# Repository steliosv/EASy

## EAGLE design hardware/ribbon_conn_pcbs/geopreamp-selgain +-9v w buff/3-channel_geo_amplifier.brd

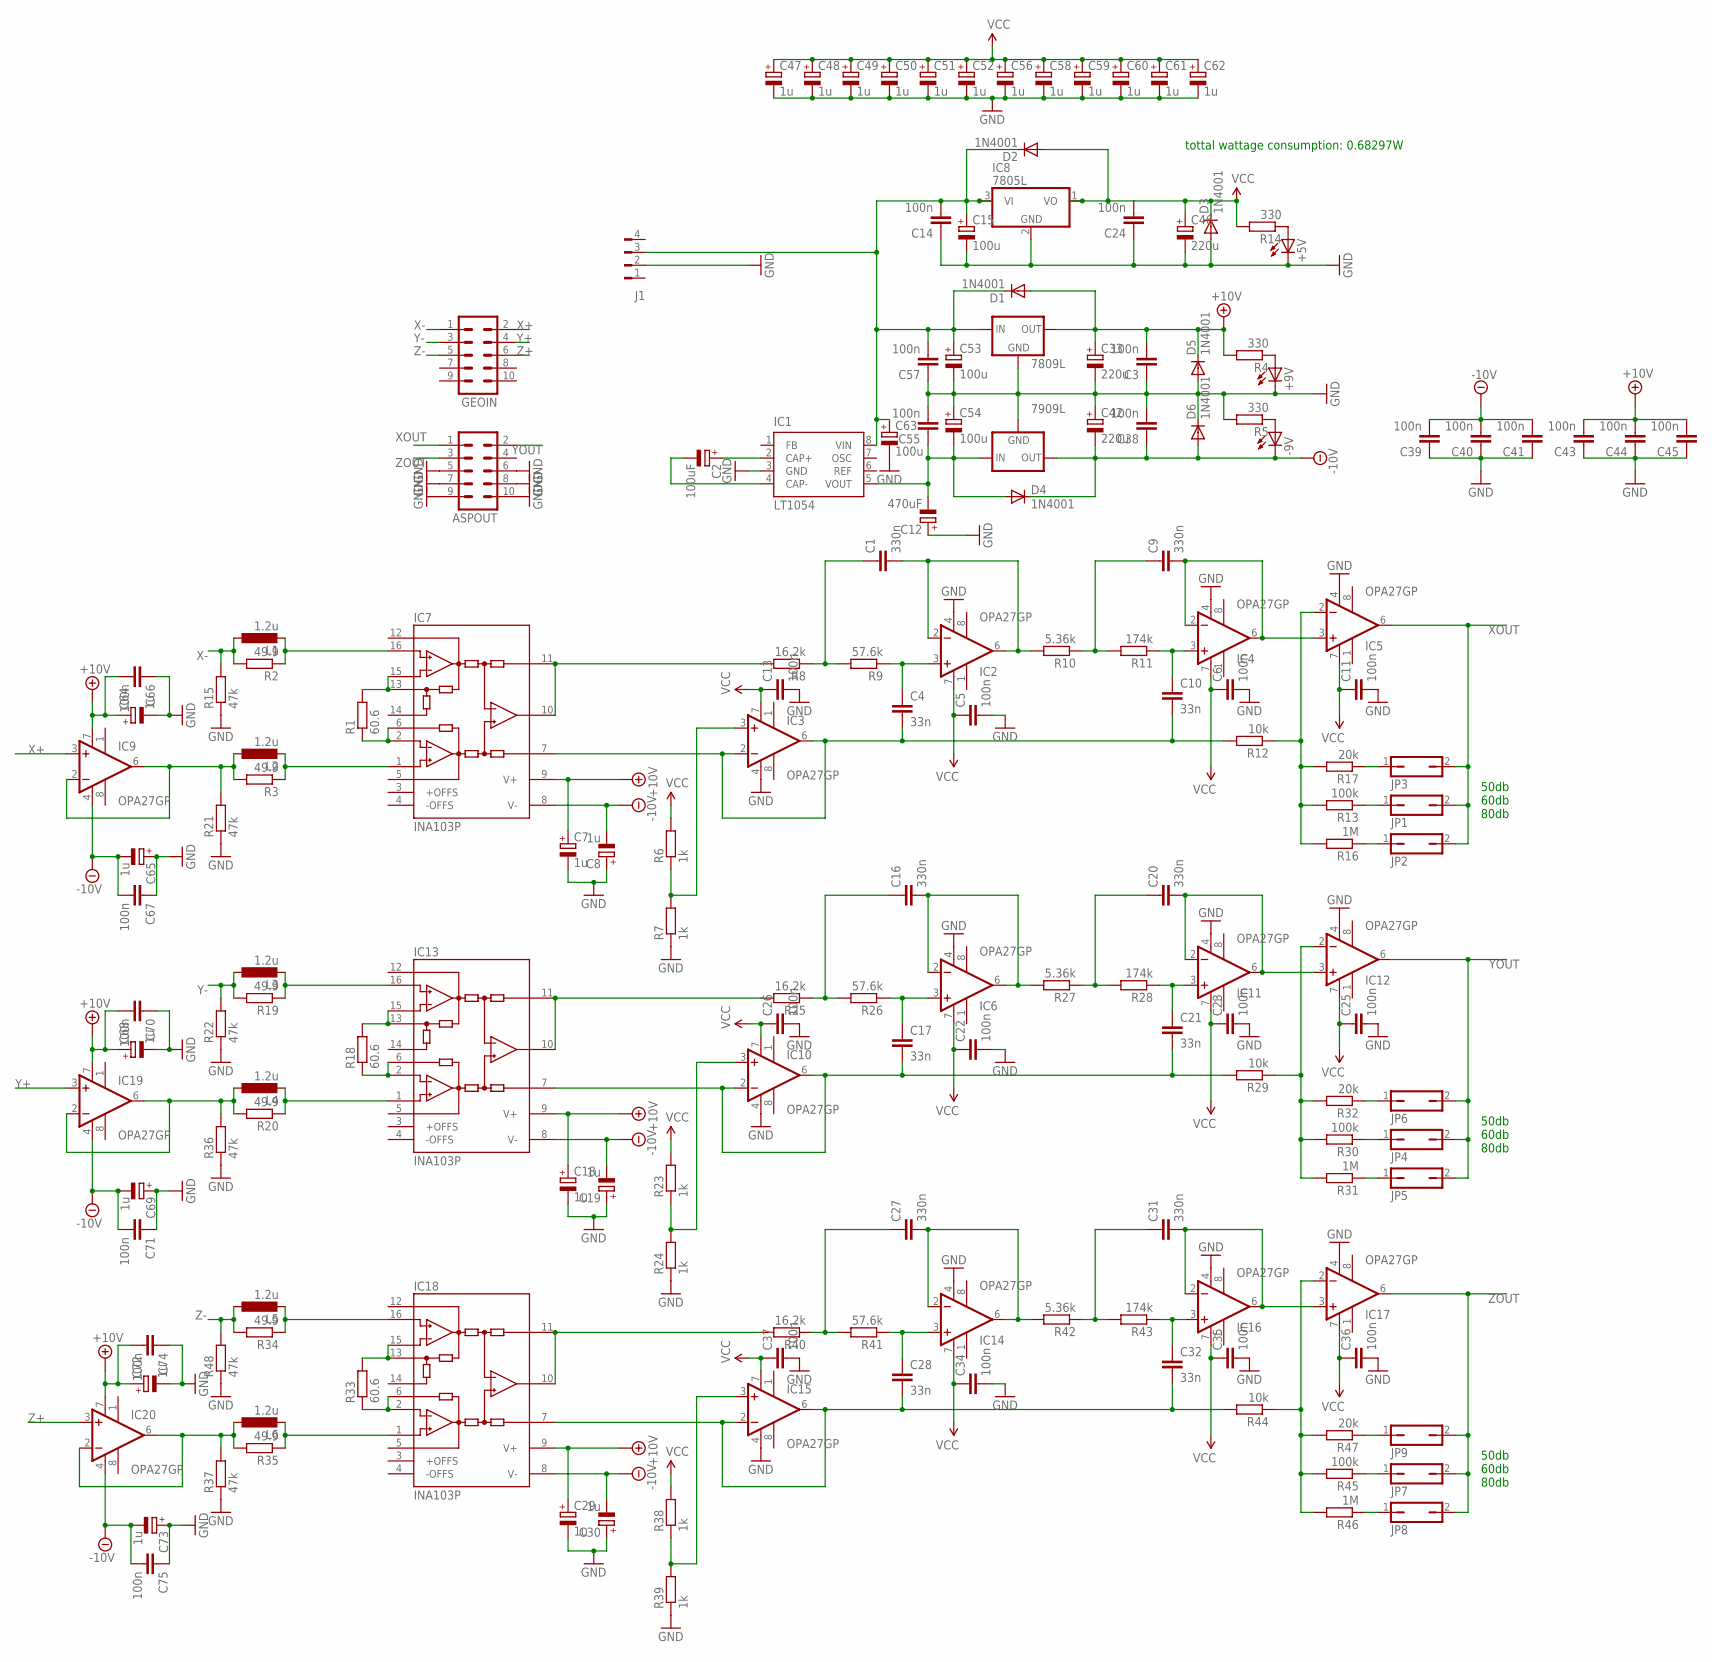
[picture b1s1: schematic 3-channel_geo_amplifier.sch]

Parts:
7809L: 78LXX
7909L: 79LXX
+5V, +9V: LED3MM
-9V: LED3MM
ASPOUT: ML10
C1, C9, C16, C20, C27, C31: 330n; C050-025X075
C2: 100uF; E2,5-7
C3, C5, C6, C11, C13, C14, C22, C23, C24, C25, C26, C34, C35, C36, C37, C38, C39, C40, C41, C43, C44, C45, C55, C57, C66, C67, C70, C71, C74, C75: 100n; C050-025X075
C4, C10, C17, C21, C28, C32: 33n; C050-025X075
C7, C8, C18, C19, C29, C30, C47, C48, C49, C50, C51, C52, C56, C58, C59, C60, C61, C62, C64, C65, C68, C69, C72, C73: 1u; B45181A
C12: 470uF; E5-8,5
C15: 100u; E2,5-7
C33, C42: 220u; E2,5-5
C46: 220u; E2,5-7
C53, C54, C63: 100u; E2,5-5
D1, D2, D3, D4, D5, D6: 1N4001; DO41-10
GEOIN: ML10
IC1: LT1054; DIL8
IC2, IC3, IC4, IC5, IC6, IC9, IC10, IC11, IC12, IC14, IC15, IC16, IC17, IC19, IC20: OPA27GP; DIL08
IC7, IC13, IC18: INA103P; DIL16
IC8: 7805L; TO92
J1: FLOP-4W827001; 827001
JP1, JP2, JP3, JP4, JP5, JP6, JP7, JP8, JP9: JP1Q; JP1
L1, L2, L3, L4, L5, L6: 1.2u; 0207/10
R1, R18, R33: 60.6; 0207/10
R2, R3, R19, R20, R34, R35: 49.9; 0207/10
R4, R5, R14: 330; 0207/10
R6, R7, R23, R24, R38, R39: 1k; 0207/10
R8, R25, R40: 16.2k; 0207/10
R9, R26, R41: 57.6k; 0207/10
R10, R27, R42: 5.36k; 0207/10
R11, R28, R43: 174k; 0207/10
R12, R29, R44: 10k; 0207/10
R13, R30, R45: 100k; 0207/10
R15, R21, R22, R36, R37, R48: 47k; 0207/10
R16, R31, R46: 1M; 0207/10
R17, R32, R47: 20k; 0207/10

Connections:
+10V: 7809L.OUT, C3.2, C7.+, C18.+, C29.+, C33.+, C43.2, C44.2, C45.2, C64.+, C66.2, C68.+, C70.2, C72.+, C74.2, D1.A, D5.C, IC7.9 (V+), IC9.7 (V+), IC13.9 (V+), IC18.9 (V+), IC19.7 (V+), IC20.7 (V+), R4.2
-10V: 7909L.OUT, -9V.K (C), C8.-, C19.-, C30.-, C38.1, C39.2, C40.2, C41.2, C42.-, C65.-, C67.2, C69.-, C71.2, C73.-, C75.2, D4.C, D6.A, IC7.8 (V-), IC9.4 (V-), IC13.8 (V-), IC18.8 (V-), IC19.4 (V-), IC20.4 (V-)
A: IC20.2 (-IN), IC20.6 (OUT), L6.1, R35.2, R37.2
GND: 7809L.GND, 7909L.GND, +5V.K (C), +9V.K (C), ASPOUT.5, ASPOUT.6, ASPOUT.7, ASPOUT.8, ASPOUT.9, ASPOUT.10, C3.1, C5.2, C6.2, C7.-, C8.+, C11.2, C12.+, C13.2, C14.1, C15.-, C18.-, C19.+, C22.2, C23.2, C24.1, C25.2, C26.2, C29.-, C30.+, C33.-, C34.2, C35.2, C36.2, C37.2, C38.2, C39.1, C40.1, C41.1, C42.+, C43.1, C44.1, C45.1, C46.-, C47.-, C48.-, C49.-, C50.-, C51.-, C52.-, C53.-, C54.+, C55.2, C56.-, C57.1, C58.-, C59.-, C60.-, C61.-, C62.-, C63.-, C64.-, C65.+, C66.1, C67.1, C68.-, C69.+, C70.1, C71.1, C72.-, C73.+, C74.1, C75.1, D3.A, D5.A, D6.C, IC1.3 (GND), IC2.4 (V-), IC3.4 (V-), IC4.4 (V-), IC5.4 (V-), IC6.4 (V-), IC8.2 (GND), IC10.4 (V-), IC11.4 (V-), IC12.4 (V-), IC14.4 (V-), IC15.4 (V-), IC16.4 (V-), IC17.4 (V-), J1.2, R5.2, R7.1, R15.1, R21.1, R22.1, R24.1, R36.1, R37.1, R39.1, R48.1
unnamed: IC7.13 (-RG), IC7.15 (-GS), R1.2
unnamed: IC7.2 (+GS), IC7.6 (+RG), R1.1
unnamed: IC7.1 (+IN), L2.2, R3.1
unnamed: IC19.2 (-IN), IC19.6 (OUT), L4.1, R20.2, R36.2
unnamed: IC7.16 (-IN), L1.2, R2.1
unnamed: C4.2, C10.2, IC3.2 (-IN), IC3.6 (OUT), IC7.7 (REF), R12.2
unnamed: IC3.3 (+IN), R6.1, R7.2
unnamed: IC7.10 (OUT), IC7.11 (SENSE), R8.2
unnamed: C1.1, R8.1, R9.2
unnamed: C4.1, IC2.3 (+IN), R9.1
unnamed: C1.2, IC2.2 (-IN), IC2.6 (OUT), R10.2
unnamed: C9.2, IC4.2 (-IN), IC4.6 (OUT), IC5.3 (+IN)
unnamed: C9.1, R10.1, R11.2
unnamed: C10.1, IC4.3 (+IN), R11.1
unnamed: +5V.A, R14.1
unnamed: IC5.2 (-IN), R12.1, R13.2, R16.2, R17.2
unnamed: JP1.1, R13.1
unnamed: IC9.2 (-IN), IC9.6 (OUT), L2.1, R3.2, R21.2
unnamed: +9V.A, R4.1
unnamed: IC13.13 (-RG), IC13.15 (-GS), R18.2
unnamed: JP2.1, R16.1
unnamed: IC13.2 (+GS), IC13.6 (+RG), R18.1
unnamed: JP3.1, R17.1
unnamed: IC13.1 (+IN), L4.2, R20.1
unnamed: C2.-, IC1.4 (CAP-)
unnamed: C2.+, IC1.2 (CAP+)
unnamed: IC13.16 (-IN), L3.2, R19.1
unnamed: C17.2, C21.2, IC10.2 (-IN), IC10.6 (OUT), IC13.7 (REF), R29.2
unnamed: IC10.3 (+IN), R23.1, R24.2
unnamed: IC13.10 (OUT), IC13.11 (SENSE), R25.2
unnamed: C16.1, R25.1, R26.2
unnamed: C17.1, IC6.3 (+IN), R26.1
unnamed: C16.2, IC6.2 (-IN), IC6.6 (OUT), R27.2
unnamed: C20.1, R27.1, R28.2
unnamed: C21.1, IC11.3 (+IN), R28.1
unnamed: C20.2, IC11.2 (-IN), IC11.6 (OUT), IC12.3 (+IN)
unnamed: IC12.2 (-IN), R29.1, R30.2, R31.2, R32.2
unnamed: -9V.A, R5.1
unnamed: JP4.1, R30.1
unnamed: JP5.1, R31.1
unnamed: JP6.1, R32.1
unnamed: IC18.13 (-RG), IC18.15 (-GS), R33.2
unnamed: IC18.2 (+GS), IC18.6 (+RG), R33.1
unnamed: IC18.1 (+IN), L6.2, R35.1
unnamed: 7809L.IN, C14.2, C15.+, C53.+, C57.2, C63.+, D1.C, D2.C, IC1.8 (VIN), IC8.3 (VI), J1.3
unnamed: IC18.16 (-IN), L5.2, R34.1
unnamed: C28.2, C32.2, IC15.2 (-IN), IC15.6 (OUT), IC18.7 (REF), R44.2
unnamed: IC15.3 (+IN), R38.1, R39.2
unnamed: IC18.10 (OUT), IC18.11 (SENSE), R40.2
unnamed: C27.1, R40.1, R41.2
unnamed: C28.1, IC14.3 (+IN), R41.1
unnamed: 7909L.IN, C12.-, C54.-, C55.1, D4.A, IC1.5 (VOUT)
unnamed: C27.2, IC14.2 (-IN), IC14.6 (OUT), R42.2
unnamed: C31.1, R42.1, R43.2
unnamed: C32.1, IC16.3 (+IN), R43.1
unnamed: C31.2, IC16.2 (-IN), IC16.6 (OUT), IC17.3 (+IN)
unnamed: IC17.2 (-IN), R44.1, R45.2, R46.2, R47.2
unnamed: JP7.1, R45.1
unnamed: JP8.1, R46.1
unnamed: JP9.1, R47.1
VCC: C5.1, C6.1, C11.1, C13.1, C22.1, C23.1, C24.2, C25.1, C26.1, C34.1, C35.1, C36.1, C37.1, C46.+, C47.+, C48.+, C49.+, C50.+, C51.+, C52.+, C56.+, C58.+, C59.+, C60.+, C61.+, C62.+, D2.A, D3.C, IC2.7 (V+), IC3.7 (V+), IC4.7 (V+), IC5.7 (V+), IC6.7 (V+), IC8.1 (VO), IC10.7 (V+), IC11.7 (V+), IC12.7 (V+), IC14.7 (V+), IC15.7 (V+), IC16.7 (V+), IC17.7 (V+), R6.2, R14.2, R23.2, R38.2
X+: GEOIN.2, IC9.3 (+IN)
X-: GEOIN.1, L1.1, R2.2, R15.2
XOUT: ASPOUT.1, IC5.6 (OUT), JP1.2, JP2.2, JP3.2
Y+: GEOIN.4, IC19.3 (+IN)
Y-: GEOIN.3, L3.1, R19.2, R22.2
YOUT: ASPOUT.2, IC12.6 (OUT), JP4.2, JP5.2, JP6.2
Z+: GEOIN.6, IC20.3 (+IN)
Z-: GEOIN.5, L5.1, R34.2, R48.2
ZOUT: ASPOUT.3, IC17.6 (OUT), JP7.2, JP8.2, JP9.2

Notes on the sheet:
50db 60db 80db
tottal wattage consumption: 0.68297W

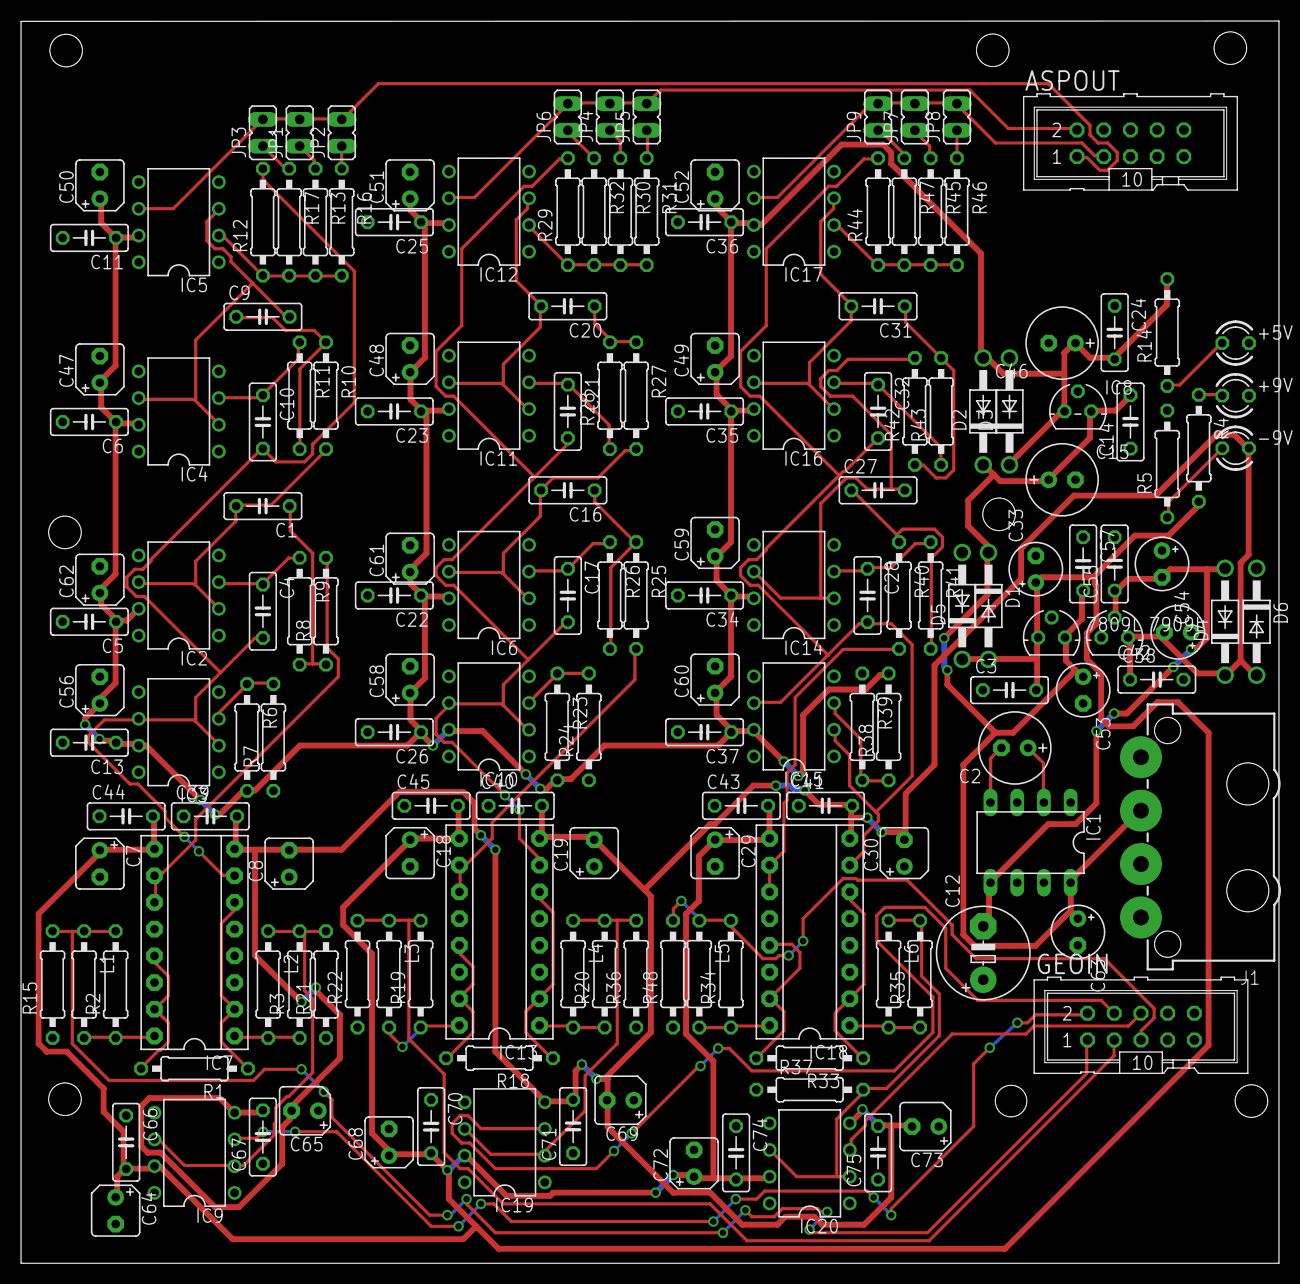
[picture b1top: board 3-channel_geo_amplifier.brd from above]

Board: 2 copper layers, 119.6 x 118.1 mm, 172 parts (0 on the bottom side), 74 nets.

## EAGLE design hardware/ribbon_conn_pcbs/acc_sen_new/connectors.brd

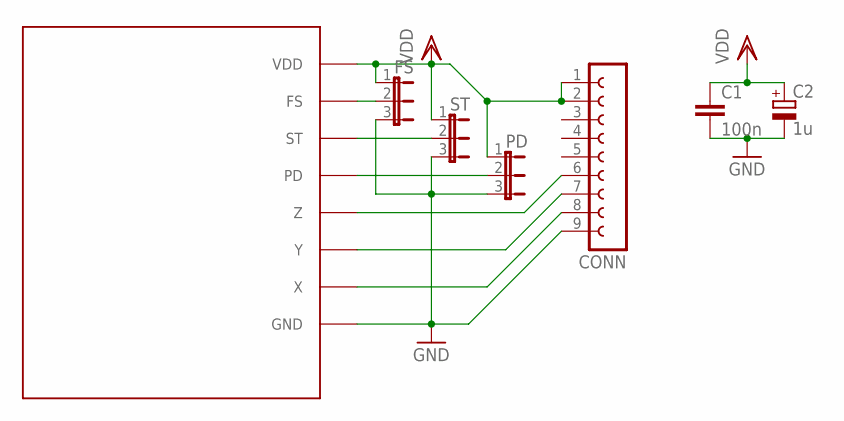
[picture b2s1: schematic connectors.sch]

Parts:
C1: 100n; C050-025X075
C2: 1u; E2-5
CONN: FE09-1; FE09
FS: JP2E; JP2
PD: JP2E; JP2
ST: JP2E; JP2
U$2: LIS; LIS344

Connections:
GND: C1.2, C2.-, CONN.9, FS.3, PD.3, ST.3, U$2.GND1 (GND), U$2.GND2 (GND), U$2.GND3 (GND), U$2.GND5 (GND)
unnamed: CONN.8, U$2.X
unnamed: FS.2, U$2.FS
unnamed: CONN.7, U$2.Y
unnamed: CONN.6, U$2.Z
unnamed: ST.2, U$2.ST
unnamed: PD.2, U$2.PD
VDD: C1.1, C2.+, CONN.1, CONN.2, FS.1, PD.1, ST.1, U$2.VDD, U$2.VDD2 (VDD)

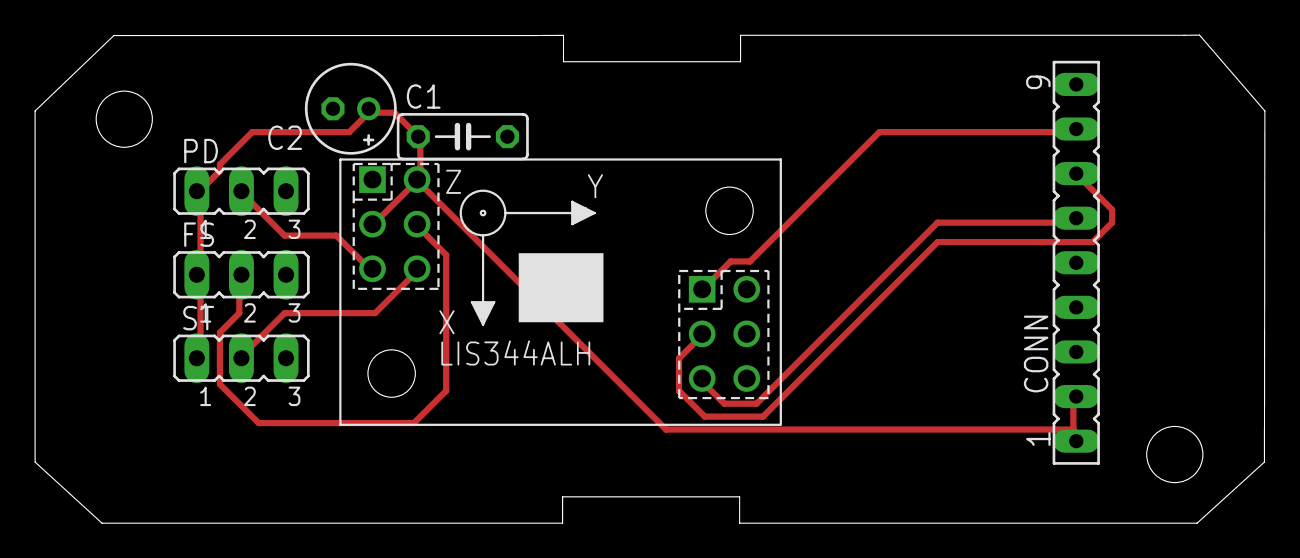
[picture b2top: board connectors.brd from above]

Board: 2 copper layers, 70.1 x 27.8 mm, 7 parts (0 on the bottom side), 8 nets.

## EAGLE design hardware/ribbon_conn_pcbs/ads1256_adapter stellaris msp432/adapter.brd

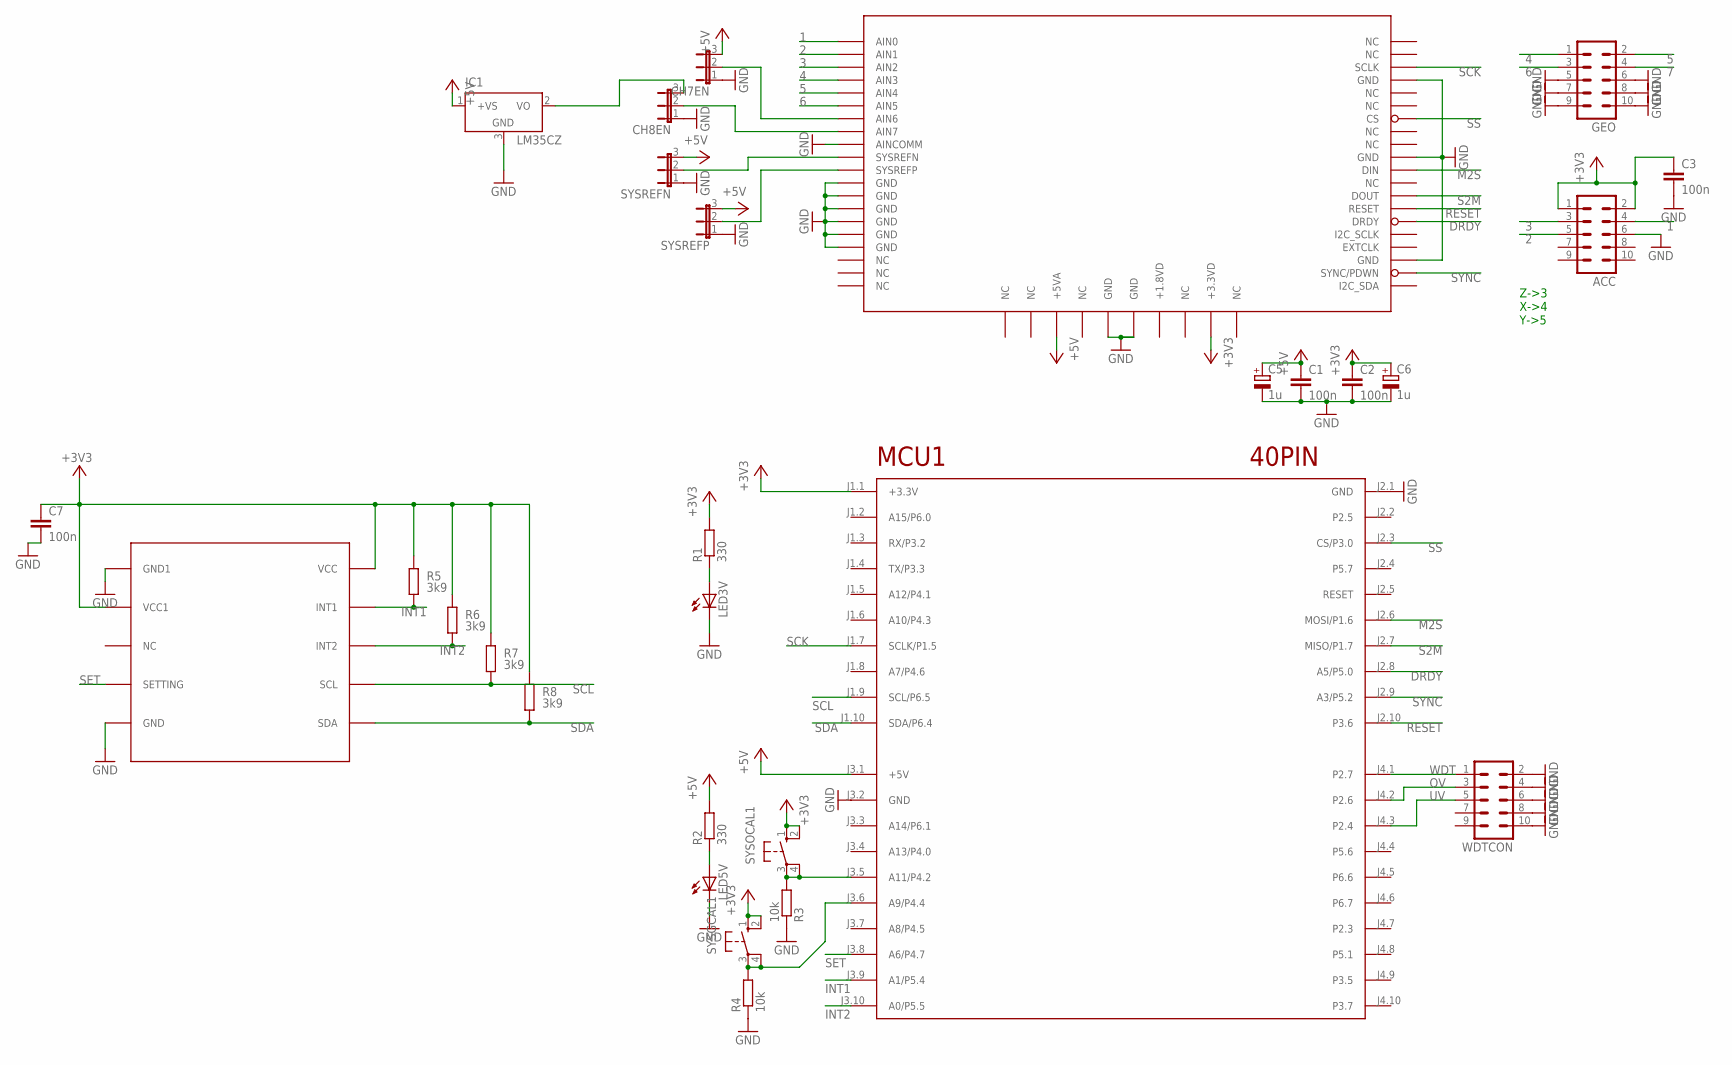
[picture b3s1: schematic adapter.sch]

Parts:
ACC: ML10
C1, C2, C3, C7: 100n; C050-025X075
C5, C6: 1u; E2,5-6E
CH7EN, CH8EN: JP2E; JP2
GEO: ML10
IC1: LM35CZ; TO92
LED3V, LED5V: LED3MM
MCU1: 40PIN
R1, R2: 330; 0207/10
R3, R4: 10k; 0207/10
R5, R6, R7, R8: 3k9; 0207/10; TOLERANCE 5%
SYSGCAL1: 10-XX; B3F-10XX
SYSOCAL1: 10-XX; B3F-10XX
SYSREFN: JP2E; JP2
SYSREFP: JP2E; JP2
U$1: D7S
U$2: ADS1256EVM
WDTCON: ML10

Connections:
1: ACC.4, U$2.J1.1 (AIN0)
2: ACC.5, U$2.J1.2 (AIN1)
3: ACC.3, U$2.J1.3 (AIN2)
4: GEO.1, U$2.J1.4 (AIN3)
5: GEO.2, U$2.J1.5 (AIN4)
6: GEO.3, U$2.J1.6 (AIN5)
7: GEO.4
+3V3: ACC.1, ACC.2, C2.1, C3.1, C6.+, C7.1, MCU1.J1.1 (+3.3V), R1.2, R5.2, R6.2, R7.2, R8.2, SYSGCAL1.1 (S), SYSGCAL1.2 (S1), SYSOCAL1.1 (S), SYSOCAL1.2 (S1), U$1.P$1 (VCC), U$1.P$9 (VCC1), U$2.J3.9 (+3.3VD)
+5V: C1.1, C5.+, CH7EN.3, IC1.1 (+VS), MCU1.J3.1 (+5V), R2.2, SYSREFN.3, SYSREFP.3, U$2.J3.3 (+5VA)
DRDY: MCU1.J2.8 (A5/P5.0), U$2.J2.15 (DRDY)
GND: ACC.6, C1.2, C2.2, C3.2, C5.-, C6.-, C7.2, CH7EN.1, CH8EN.1, GEO.5, GEO.6, GEO.7, GEO.8, GEO.9, GEO.10, IC1.3 (GND), LED3V.K (C), LED5V.K (C), MCU1.J2.1 (GND), MCU1.J3.2 (GND), R3.1, R4.1, SYSREFN.1, SYSREFP.1, U$1.P$6 (GND), U$1.P$10 (GND1), U$2.J1.9 (GND), U$2.J1.10 (AINCOMM), U$2.J1.11 (GND), U$2.J1.13 (GND), U$2.J1.15 (GND), U$2.J1.17 (GND), U$2.J1.19 (GND), U$2.J2.4 (GND), U$2.J2.10 (GND), U$2.J2.18 (GND), U$2.J3.5 (GND), U$2.J3.6 (GND), WDTCON.2, WDTCON.4, WDTCON.6, WDTCON.8, WDTCON.10
INT1: MCU1.J3.9 (A1/P5.4), R5.1, U$1.P$2 (INT1)
INT2: MCU1.J3.10 (A0/P5.5), R6.1, U$1.P$3 (INT2)
M2S: MCU1.J2.6 (MOSI/P1.6), U$2.J2.11 (DIN)
unnamed: LED3V.A, R1.1
unnamed: LED5V.A, R2.1
unnamed: CH8EN.3, IC1.2 (VO)
unnamed: CH8EN.2, U$2.J1.8 (AIN7)
unnamed: CH7EN.2, U$2.J1.7 (AIN6)
unnamed: MCU1.J3.5 (A11/P4.2), R3.2, SYSOCAL1.3, SYSOCAL1.4 (P1)
unnamed: MCU1.J3.6 (A9/P4.4), R4.2, SYSGCAL1.3, SYSGCAL1.4 (P1)
unnamed: SYSREFN.2, U$2.J1.18 (SYSREFN)
unnamed: SYSREFP.2, U$2.J1.20 (SYSREFP)
OV: MCU1.J4.2 (P2.6), WDTCON.3
RESET: MCU1.J2.10 (P3.6), U$2.J2.14 (RESET)
S2M: MCU1.J2.7 (MISO/P1.7), U$2.J2.13 (DOUT)
SCK: MCU1.J1.7 (SCLK/P1.5), U$2.J2.3 (SCLK)
SCL: MCU1.J1.9 (SCL/P6.5), R7.1, U$1.P$4 (SCL)
SDA: MCU1.J1.10 (SDA/P6.4), R8.1, U$1.P$5 (SDA)
SET: MCU1.J3.8 (A6/P4.7), U$1.P$7 (SETTING)
SS: MCU1.J2.3 (CS/P3.0), U$2.J2.7 (CS)
SYNC: MCU1.J2.9 (A3/P5.2), U$2.J2.19 (SYNC/PDWN)
UV: MCU1.J4.3 (P2.4), WDTCON.5
WDT: MCU1.J4.1 (P2.7), WDTCON.1

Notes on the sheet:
Z->3 X->4 Y->5

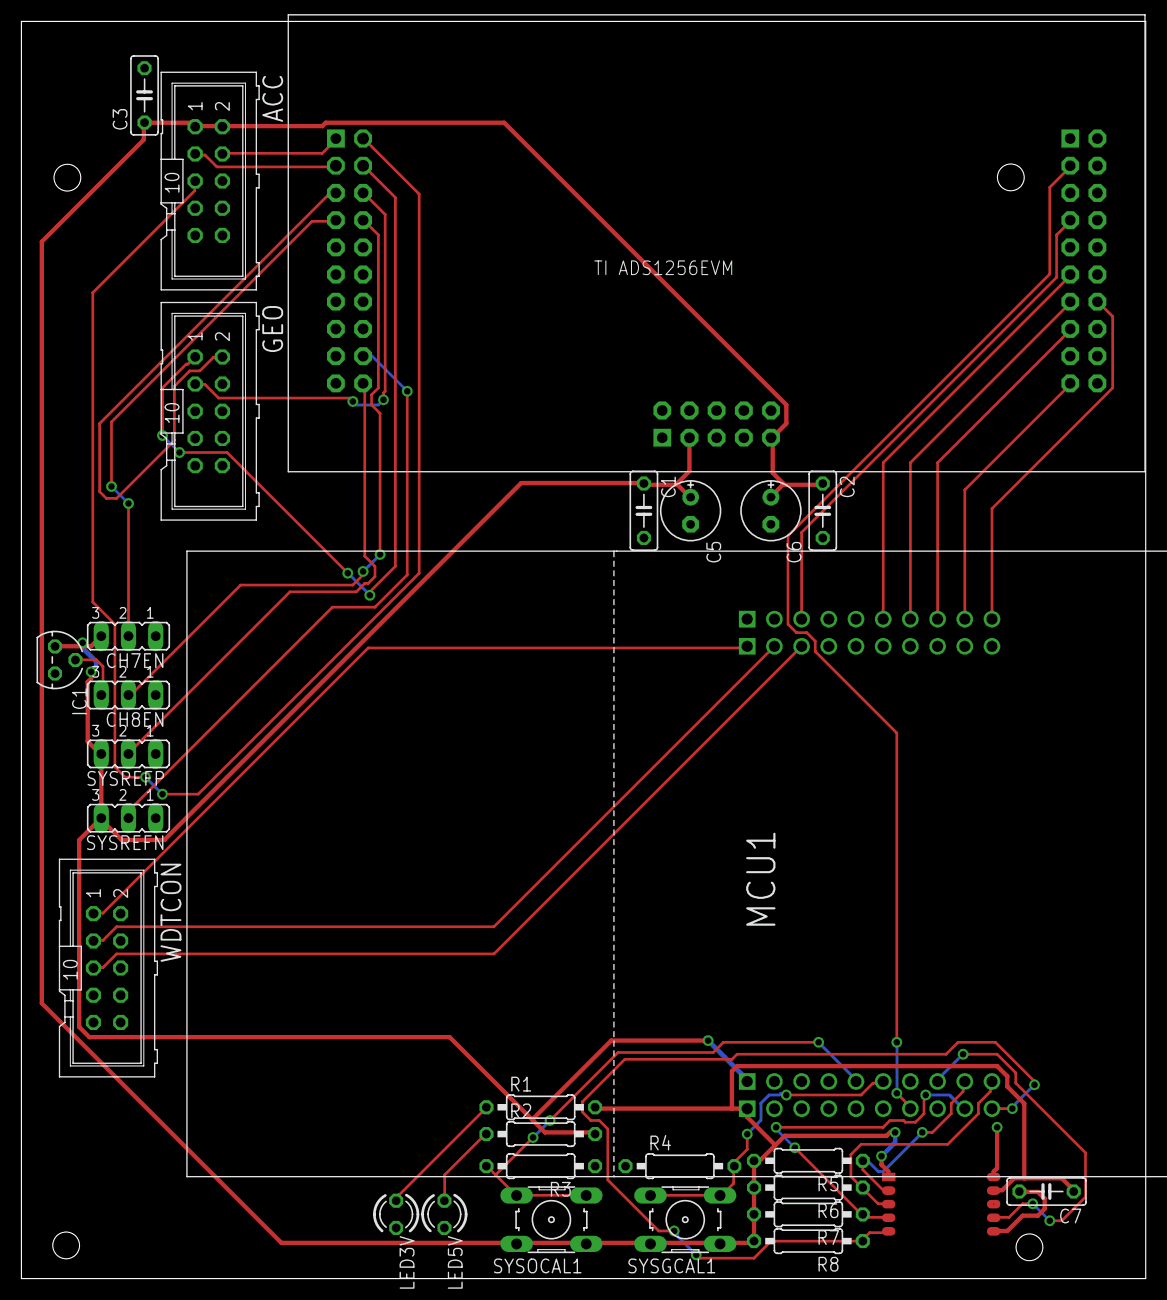
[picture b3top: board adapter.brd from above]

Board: 2 copper layers, 105.0 x 117.4 mm, 29 parts (0 on the bottom side), 33 nets.

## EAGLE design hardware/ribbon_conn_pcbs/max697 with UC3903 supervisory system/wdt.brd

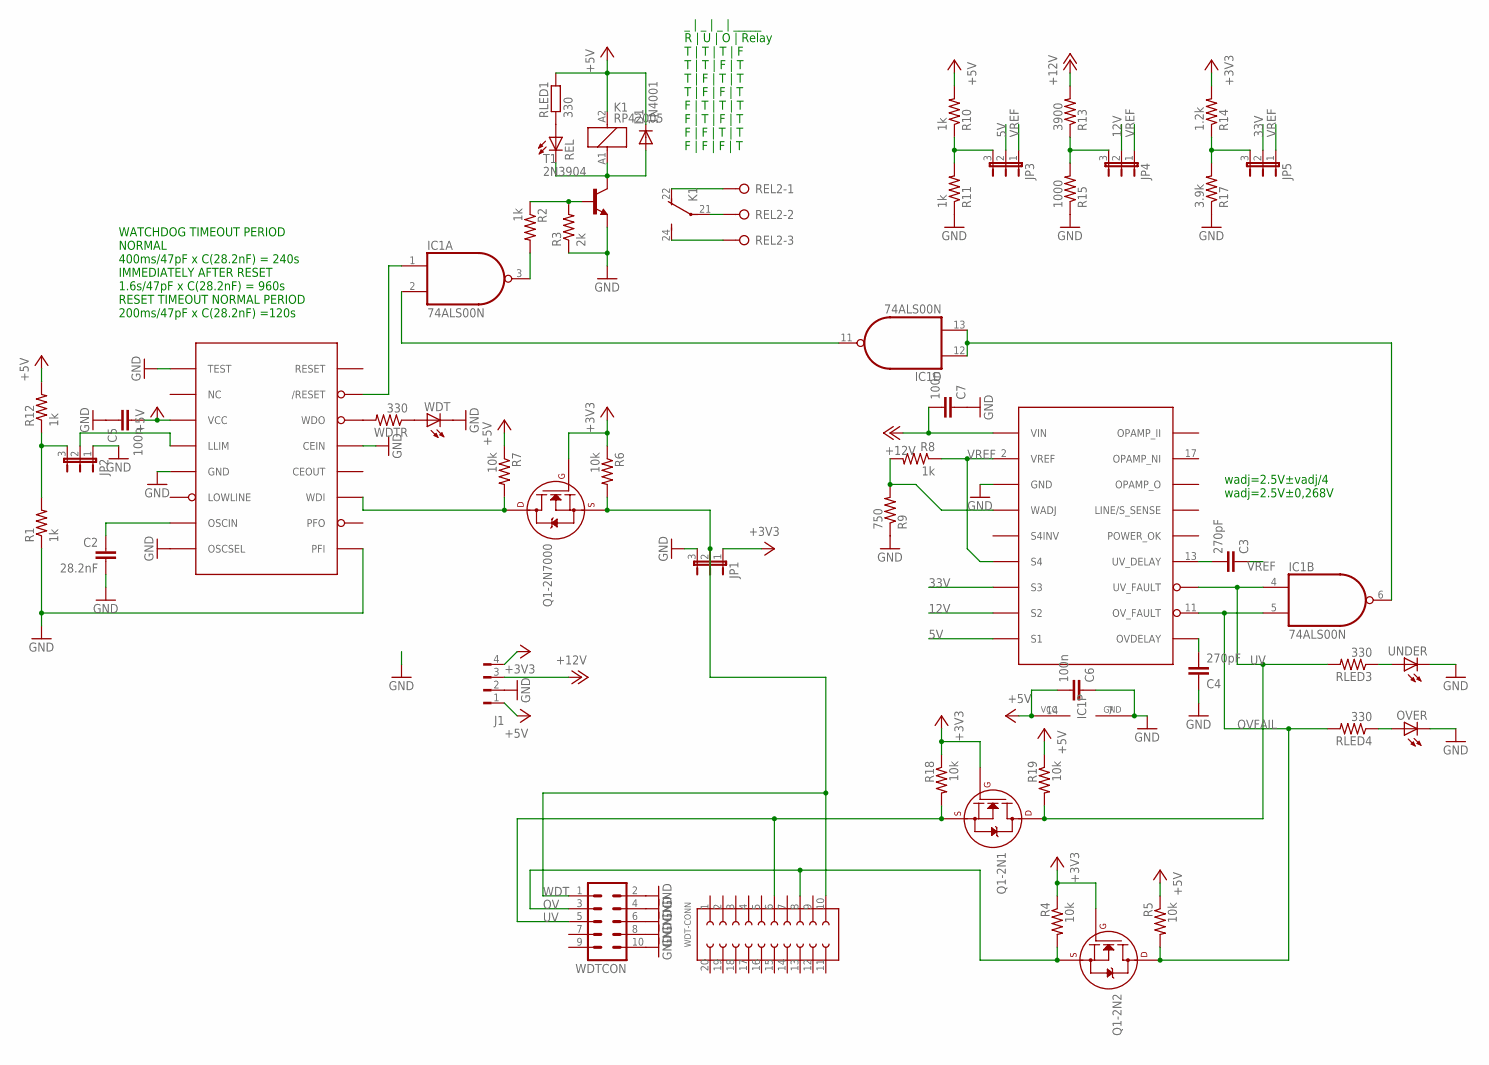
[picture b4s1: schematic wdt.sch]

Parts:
C2: 28.2nF; C050-025X075
C3, C4: 270pF; C050-025X075
C5, C6, C7: 100n; C050-025X075
D1: 1N4001; DO41-10
IC1: 74ALS00N; DIL14
J1: FLOP-4W827001; 827001
JP1, JP2, JP3, JP4, JP5: JP2E; JP2
K1: RP42005; RP420
OVER: LED3MM
Q1-2N1, Q1-2N2, Q1-2N7000: 2N7000_TO92; TO-92
R1, R2, R8, R10, R11, R12: 1k; 0207/10
R3: 2k; 0207/10
R4, R5, R6, R7, R18, R19: 10k; 0207/10
R9: 750; 0207/10
R13: 3900; 0207/10
R14: 1.2k; 0207/10
R15: 1000; 0207/10
R17: 3.9k; 0207/10
REL: LED3MM
REL2: W237-3E
RLED1, RLED3, RLED4: 330; 0207/10
T1: 2N3904; TO92
U$1: UC3903; DIL18
U$2: MAX697; DIL16
UNDER: LED3MM
WDT: LED3MM
WDT-CONN: 623X2021021
WDTCON: ML10
WDTR: 330; 0207/10

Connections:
5V: JP3.2, U$1.9 (S1)
12V: JP4.2, U$1.8 (S2)
33V: JP5.2, U$1.7 (S3)
+3V3: J1.4, JP1.1, Q1-2N1.2 (G), Q1-2N2.2 (G), Q1-2N7000.2 (G), R4.1, R6.1, R14.2, R18.1
+5V: C5.2, C6.2, D1.C, IC1.14 (VCC), J1.1, K1.A2 (1), R5.1, R7.1, R10.2, R12.2, R19.1, RLED1.2, U$2.3 (VCC)
+12V: C7.2, J1.3, R13.2, U$1.1 (VIN)
GND: C2.2, C4.1, C5.1, C6.1, C7.1, IC1.7 (GND), J1.2, JP1.3, JP2.1, OVER.K (C), R1.1, R3.1, R9.1, R11.1, R15.1, R17.1, T1.3 (E), U$1.3 (GND), U$2.1 (TEST), U$2.5 (GND), U$2.8 (OSCSEL), U$2.9 (PFI), U$2.13 (CEIN), UNDER.K (C), WDT.K (C), WDTCON.2, WDTCON.4, WDTCON.6, WDTCON.8, WDTCON.10
unnamed: Q1-2N7000.3 (D), R7.2, U$2.11 (WDI)
unnamed: D1.A, K1.A1 (2), REL.K (C), T1.1 (C)
unnamed: IC1.1 (I0), U$2.15 (/RESET)
unnamed: JP5.3, R14.1, R17.2
unnamed: JP2.2, U$2.4 (LLIM)
unnamed: JP3.3, R10.1, R11.2
unnamed: U$2.14 (WDO), WDTR.2
unnamed: IC1.3 (O), R2.2
unnamed: K1.22 (O), REL2.1
unnamed: R2.1, R3.2, T1.2 (B)
unnamed: REL.A, RLED1.1
unnamed: K1.21, REL2.2
unnamed: K1.24 (S), REL2.3
unnamed: R8.2, R9.2, U$1.4 (WADJ)
unnamed: JP4.3, R13.1, R15.2
unnamed: C3.2, U$1.13 (UV_DELAY)
unnamed: C4.2, U$1.10 (OVDELAY)
unnamed: IC1.2 (I1), IC1.11 (O)
unnamed: WDT.A, WDTR.1
unnamed: C2.1, U$2.7 (OSCIN)
unnamed: JP2.3, R1.2, R12.1
unnamed: IC1.6 (O), IC1.12 (I0), IC1.13 (I1)
unnamed: RLED3.1, UNDER.A
unnamed: OVER.A, RLED4.1
OV: Q1-2N2.1 (S), R4.2, WDT-CONN.8, WDTCON.3
OVFAIL: IC1.5 (I1), Q1-2N2.3 (D), R5.2, RLED4.2, U$1.11 (OV_FAULT)
UV: IC1.4 (I0), Q1-2N1.1 (S), Q1-2N1.3 (D), R18.2, R19.2, RLED3.2, U$1.12 (UV_FAULT), WDT-CONN.6, WDTCON.5
VREF: C3.1, JP3.1, JP4.1, JP5.1, R8.1, U$1.2 (VREF), U$1.6 (S4)
WDT: JP1.2, Q1-2N7000.1 (S), R6.2, WDT-CONN.10, WDTCON.1

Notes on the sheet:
wadj=2.5V±vadj/4 wadj=2.5V±0,268V
_ | _ | _ | _____ R | U | O | Relay T | T | T | F T | T | F | T T | F | T | T T | F | F | T F | T | T | T F | T | F | T F | F | T | T F | F | F | T
WATCHDOG TIMEOUT PERIOD NORMAL 400ms/47pF x C(28.2nF) = 240s IMMEDIATELY AFTER RESET 1.6s/47pF x C(28.2nF) = 960s RESET TIMEOUT NORMAL PERIOD 200ms/47pF x C(28.2nF) =120s

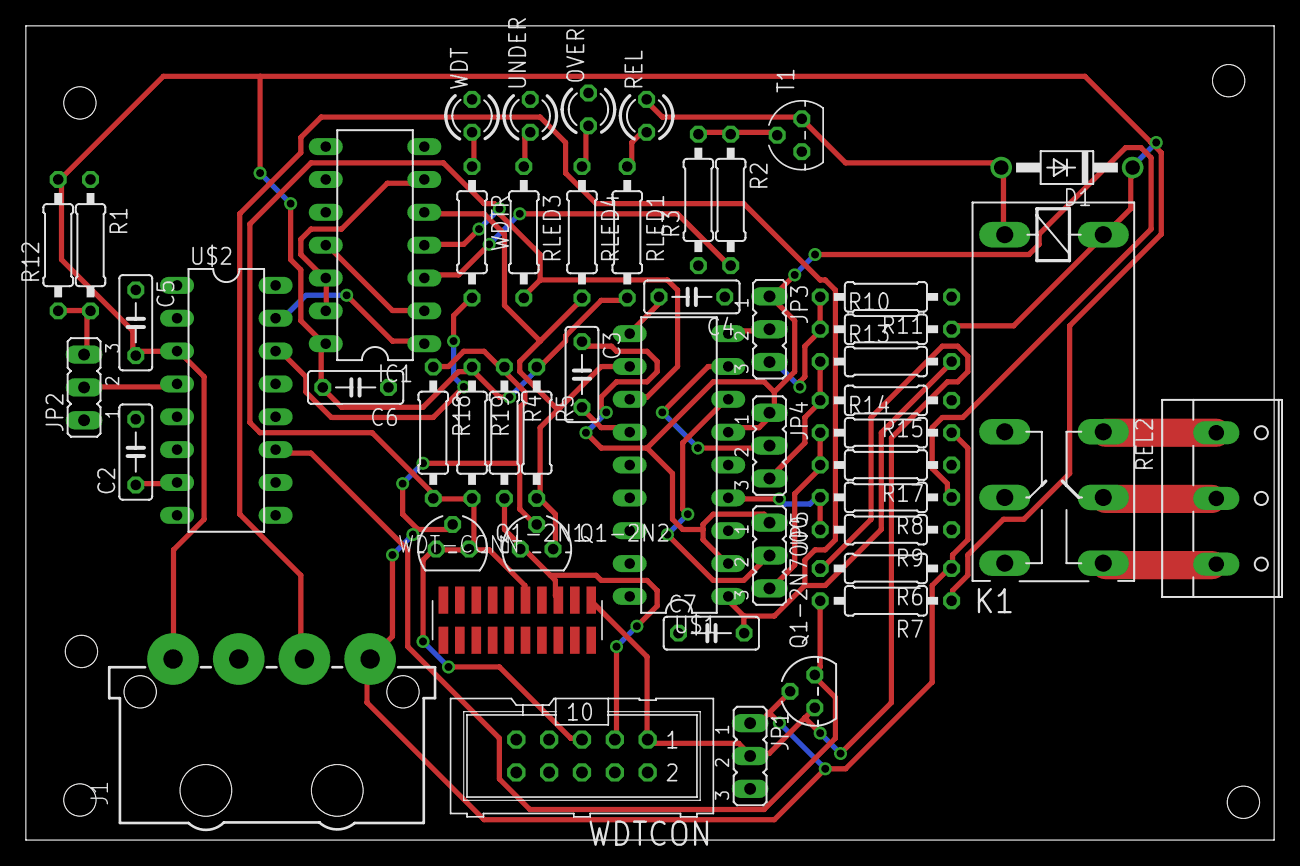
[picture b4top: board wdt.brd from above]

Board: 2 copper layers, 96.5 x 63.0 mm, 50 parts (0 on the bottom side), 36 nets.

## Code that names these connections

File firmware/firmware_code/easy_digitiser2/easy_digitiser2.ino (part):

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#include <stdlib.h>
#include <driverlib/timer_a.h>
#include <driverlib/interrupt.h>
#define NVIC_ISER0                                         (HWREG32(0xE000E100)) /* Irq 0 to 31 Set Enable Register */

unsigned long count  = 0;
unsigned long prevTime = 0;
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const int CS_PIN = 18; //Chip Select active low
const int MISO_PIN = 14; //MISO
const int MOSI_PIN = 15; //MOSI
const int DRDY_PIN = 13; //DATA READY
const int SYNC_PIN = 12; //syncronisation power down active low
const int RESET_PIN = 11; //RESET PIN active low
const int BUTTON1 = PUSH1;
const int BUTTON2 = PUSH2;
const int SYSOCAL_PIN = 25; //pin that performs System Offset Calibration
const int SYSGCAL_PIN = 26; //pin that performs System Gain Calibration
const int WDT_PIN = 40;//pin that "pets" the watchdog timer
const int OV_PIN = 39;//pin that informs for Overvoltage failure
const int UV_PIN = 38;//pin that informs for Undervoltage failure
const int RS_PIN = A15;//pin that enables reed solomon encoding
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  pinMode(RS_PIN, INPUT);
  pinMode(OV_PIN, INPUT_PULLUP);
  pinMode(UV_PIN, INPUT_PULLUP);
  pinMode(WDT_PIN, OUTPUT);
  if (digitalRead(RS_PIN)) {
    RSState = true;
  } else {
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  delay(1000);               // wait for a second
  digitalWrite(LEDG, LOW);
  digitalWrite(LEDB, HIGH);
  ads1256.begin(DRDY_PIN, CS_PIN, RESET_PIN, SYNC_PIN);
  //GPIO pins set as outputs to decrease power dissipation
  ads1256.setDeviceReady(ADS1256_DRATE_1000SPS, ADS1256_GAIN_1, GPIO_IIIO); //after assigning a PGA value and Data rate, Calibration is needed
  ads1256.setChannel(1 , COM);
  delay(1000);               // wait for a second
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/** @brief Resets the WDT (MAX697) every 10sec
*/
void wdtSnooze() {
  digitalWrite(WDT_PIN, (WDTState) ? HIGH : LOW);
  WDTState = !WDTState;
}

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
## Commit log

2020-01-28 first commit
    first commit

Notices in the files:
parts and their libraries:
Wurth_Elektronik_Electromechanic_Board_t: Copyright: Würth Elektronik
